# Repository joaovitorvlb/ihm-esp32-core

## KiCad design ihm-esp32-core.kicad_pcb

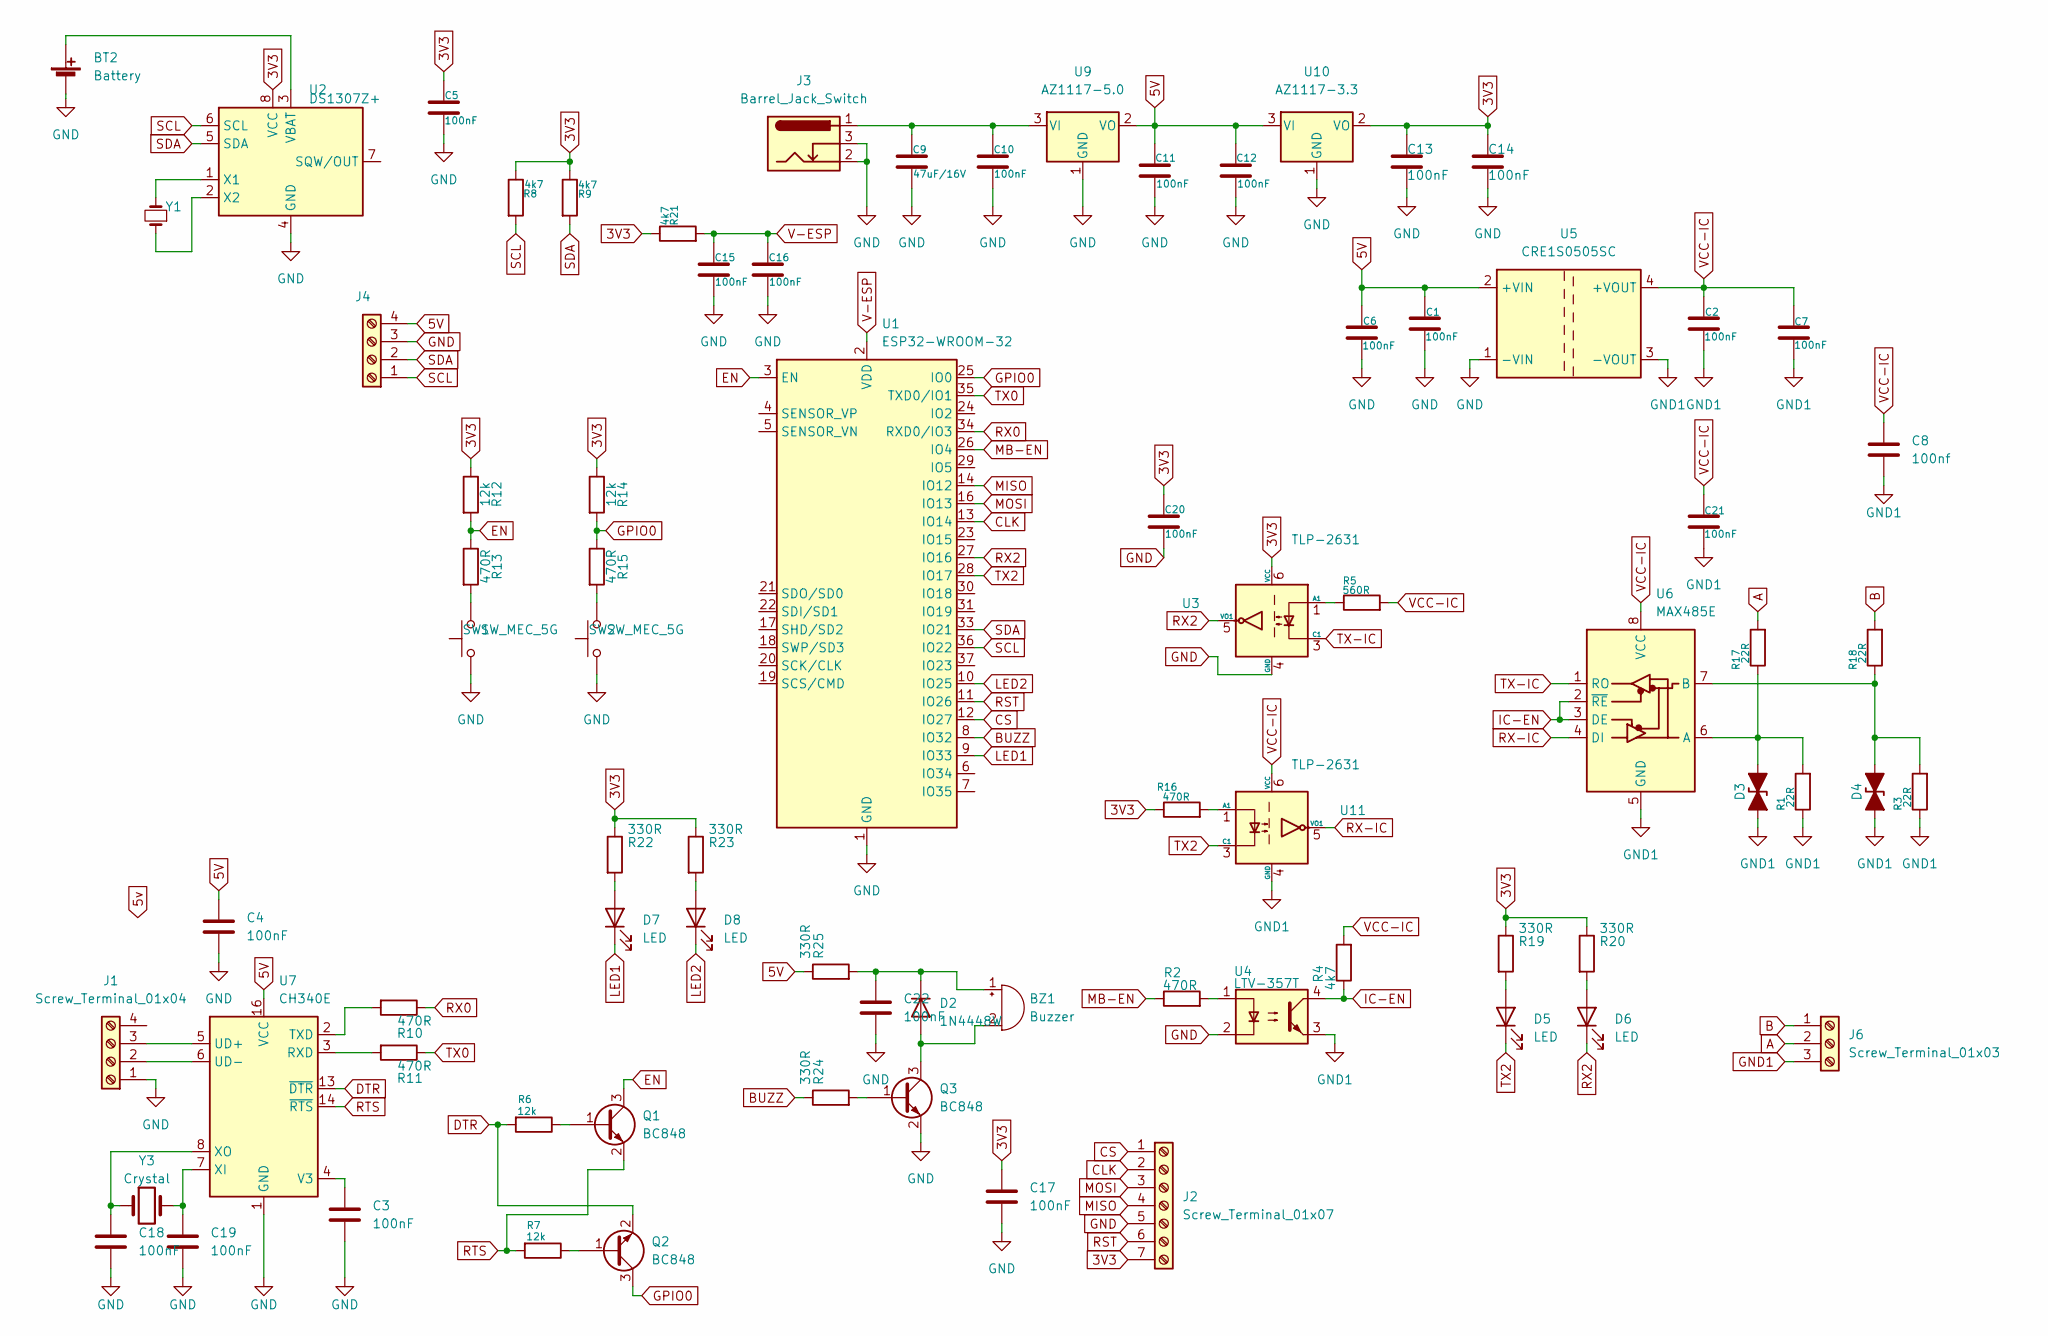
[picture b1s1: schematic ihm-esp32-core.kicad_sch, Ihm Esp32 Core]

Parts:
BT2: Battery; CASE-CR2032-VER
BZ1: Buzzer; Buzzer_12x9.5RM7.6
C1, C2, C3, C4, C5, C6, C7, C10, C11, C12, C13, C14, C15, C16, C17, C18, C19, C20, C21, C22: 100nF; C_0805_2012Metric
C8: 100nf; C_0805_2012Metric
C9: 47uF/16V; C_1210_3225Metric
D2: 1N4448W; D_SOD-123
D3, D4: D_TVS_Filled; D_SOD-128
D5, D6, D7, D8: LED; LED_0805_2012Metric_Pad1.15x1.40mm_HandSolder
J1, J4: Screw_Terminal_01x04; kk-2.54-4P
J2: Screw_Terminal_01x07; kk-2.54-7P
J3: Barrel_Jack_Switch; BarrelJack_GCT_DCJ200-10-A_Horizontal
J6: Screw_Terminal_01x03; KF128L-3.5-3P
Q1, Q2, Q3: BC848; SOT-23
R1, R3, R17, R18: 22R; R_0805_2012Metric
R2, R10, R11, R13, R15, R16: 470R; R_0805_2012Metric
R4, R8, R9: 4k7; R_0805_2012Metric
R5: 560R; R_0805_2012Metric
R6, R7, R12, R14: 12k; R_0805_2012Metric
R19, R20, R22, R23, R24, R25: 330R; R_0805_2012Metric
R21: 4k7; R_1206_3216Metric
SW1, SW2: SW_MEC_5G; SW_DIP_SPSTx01_Slide_6.7x4.1mm_W6.73mm_P2.54mm_LowProfile_J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
U1: ESP32-WROOM-32
U2: DS1307Z+; SOIC-8_3.9x4.9mm_P1.27mm
U3, U11: TLP-2631; SO-5_4.4x3.6mm_P1.27mm
U4: LTV-357T; SO-4_4.4x3.6mm_P2.54mm
U5: CRE1S0505SC; Converter_DCDC_Murata_CRE1xxxxxxSC_THT
U6: MAX485E; PowerIntegrations_SO-8
U7: CH340E; SO-16_3.9x9.9mm_P1.27mm
U9: AZ1117-5.0; SOT-223
U10: AZ1117-3.3; SOT-223
Y1: Crystal_Small; Crystal_AT310_D3.0mm_L10.0mm_Horizontal_1EP_style1
Y3: Crystal; SMD2520-4P

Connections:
3V3: C5.1, C13.1, C14.1, C17.1, C20.1, J2.7, R8.1, R9.1, R12.1, R14.1, R16.1, R19.1, R20.1, R21.1, R22.1, R23.1, U2.8 (VCC), U3.6 (VCC), U10.2 (VO)
5V: C1.1, C4.1, C6.1, C11.1, C12.1, J4.4, R25.1, U5.2 (+VIN), U7.16 (VCC), U9.2 (VO), U10.3 (VI)
A: J6.2, R17.2
B: J6.1, R18.2
BUZZ: R24.1, U1.8 (IO32)
CLK: J2.2, U1.13 (IO14)
CS: J2.1, U1.12 (IO27)
DTR: Q2.2 (E), R6.2, U7.13 (~DTR)
EN: Q1.3 (C), R12.2, R13.1, U1.3 (EN)
GND: BT2.2 (-), C1.2, C3.2, C4.2, C5.2, C6.2, C9.2, C10.2, C11.2, C12.2, C13.2, C14.2, C15.2, C16.2, C17.2, C18.2, C19.2, C20.2, C22.2, J1.1, J2.5, J3.2, J3.3, J4.3, Q3.2 (E), SW1.1 (A), SW2.1 (A), U1.1 (GND), U1.15 (GND), U1.38 (GND), U1.39 (GND), U2.4 (GND), U3.4 (GND), U4.2, U5.1 (-VIN), U7.1 (GND), U9.1 (GND), U10.1 (GND)
GND1: C2.2, C7.2, C8.2, C21.2, D3.1 (A1), D4.1 (A1), J6.3, R1.1, R3.1, U4.3, U5.3 (-VOUT), U6.5 (GND), U11.4 (GND)
GPIO0: Q2.3 (C), R14.2, R15.1, U1.25 (IO0)
IC-EN: R4.1, U4.4, U6.2 (~RE), U6.3 (DE)
LED1: D7.1 (K), U1.9 (IO33)
LED2: D8.1 (K), U1.10 (IO25)
MB-EN: R2.1, U1.26 (IO4)
MISO: J2.4, U1.14 (IO12)
MOSI: J2.3, U1.16 (IO13)
unnamed: BT2.1 (+), U2.3 (VBAT)
unnamed: BZ1.2 (+), D2.2 (A), Q3.3 (C)
unnamed: BZ1.1 (-), C22.1, D2.1 (K), R25.2
unnamed: D3.2 (A2), R1.2, R17.1, U6.6 (A)
unnamed: D4.2 (A2), R3.2, R18.1, U6.7 (B)
unnamed: D5.2 (A), R19.2
unnamed: D6.2 (A), R20.2
unnamed: D7.2 (A), R22.2
unnamed: D8.2 (A), R23.2
unnamed: J1.2, U7.6 (UD-)
unnamed: J1.3, U7.5 (UD+)
unnamed: Q1.1 (B), R6.1
unnamed: Q2.1 (B), R7.1
unnamed: Q3.1 (B), R24.2
unnamed: R2.2, U4.1
unnamed: R13.2, SW1.2 (B)
unnamed: R15.2, SW2.2 (B)
unnamed: U2.1 (X1), Y1.2
unnamed: U2.2 (X2), Y1.1
unnamed: R5.1, U3.1 (A1)
unnamed: R11.2, U7.3 (RXD)
unnamed: R10.2, U7.2 (TXD)
unnamed: C3.1, U7.4 (V3)
unnamed: C19.1, U7.7 (XI), Y3.3 (2)
unnamed: C18.1, U7.8 (XO), Y3.1
unnamed: C9.1, C10.1, J3.1, U9.3 (VI)
unnamed: R16.2, U11.1 (A1)
RST: J2.6, U1.11 (IO26)
RTS: Q1.2 (E), R7.2, U7.14 (~RTS)
RX0: R10.1, U1.34 (RXD0/IO3)
RX2: D6.1 (K), U1.27 (IO16), U3.5 (VO1)
RX-IC: U6.4 (DI), U11.5 (VO1)
SCL: J4.1, R8.2, U1.36 (IO22), U2.6 (SCL)
SDA: J4.2, R9.2, U1.33 (IO21), U2.5 (SDA)
TX0: R11.1, U1.35 (TXD0/IO1)
TX2: D5.1 (K), U1.28 (IO17), U11.3 (C1)
TX-IC: U3.3 (C1), U6.1 (RO)
V-ESP: C15.1, C16.1, R21.2, U1.2 (VDD)
VCC-IC: C2.1, C7.1, C8.1, C21.1, R4.2, R5.2, U5.4 (+VOUT), U6.8 (VCC), U11.6 (VCC)

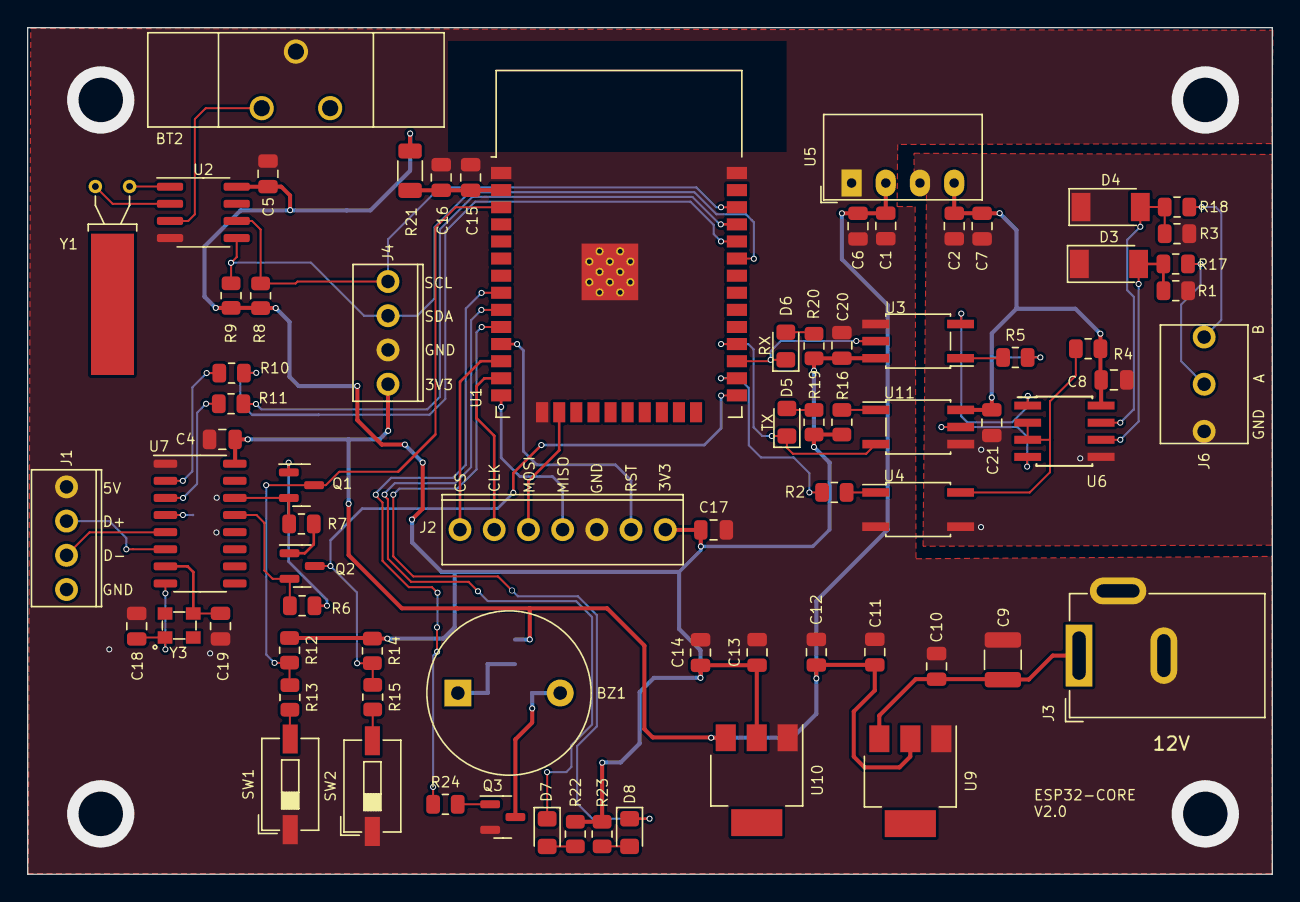
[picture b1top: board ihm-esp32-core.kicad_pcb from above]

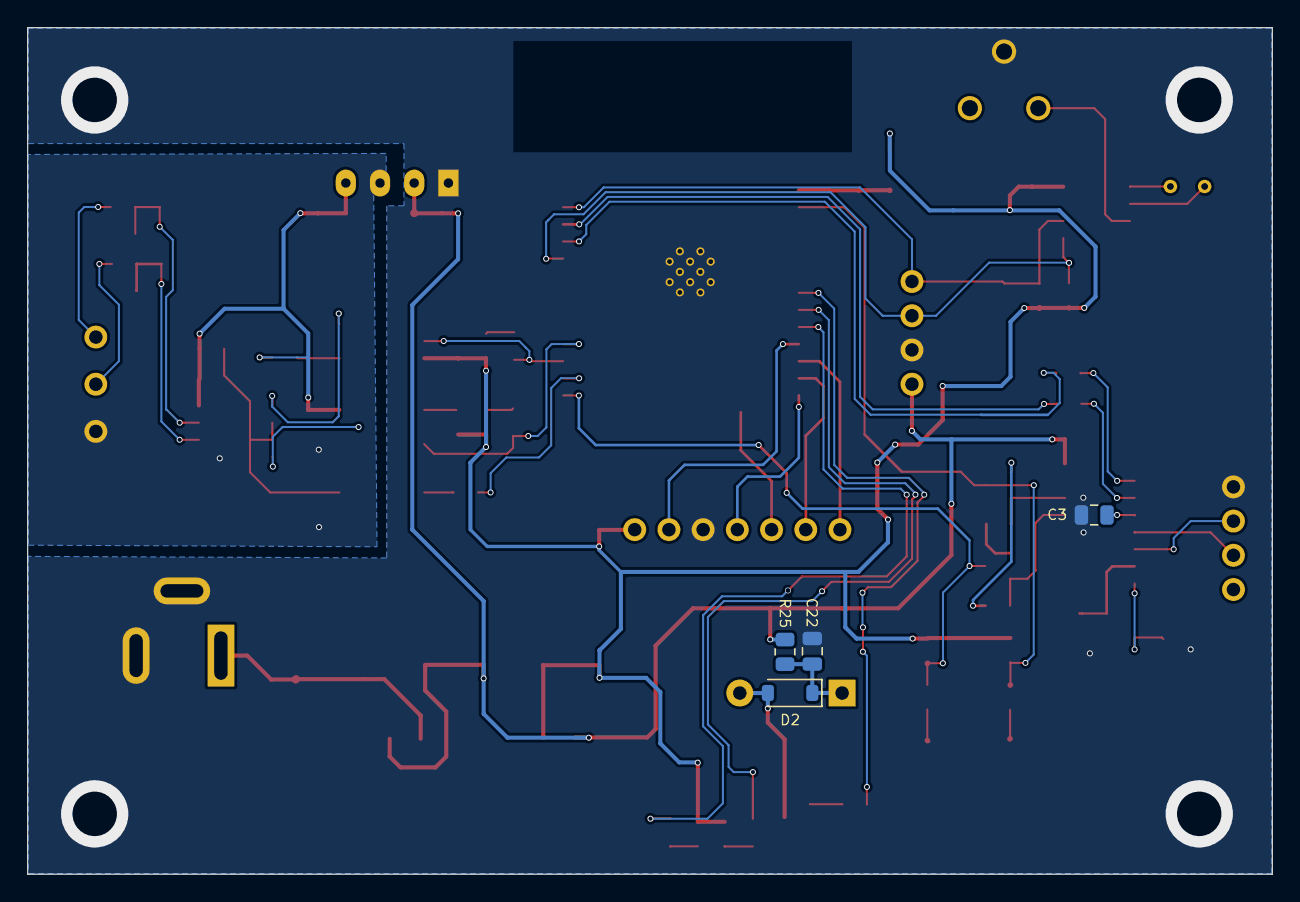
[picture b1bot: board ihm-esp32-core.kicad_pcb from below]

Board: 2 copper layers, 92.4 x 62.9 mm, 78 parts (4 on the bottom side), 57 nets.

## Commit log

2023-06-23 Preparando para a release v1.0
2023-06-23 Preparando para a release v2.0
